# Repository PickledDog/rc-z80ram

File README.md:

# rc-z80ram
 CPU+RAM+Clock+Reset for RC2014

## Overview
This RC2014-compatible card provides a Z80 CPU, pageable RAM (fixed at the full 64K memory space, but disableable by the PAGE signal), and CLK and CLK2 signals. Reset supervision is provided.

## CPU
CPU is a regular Z80, with all signals brought out to the RC2014 Enhanced bus. Clock is always connected to the bus (and optionally generated locally - see below).

## Memory
RAM is provided by a single AS6C1008 128k x 8 SRAM chip. The chip may be optionally disabled (with JP1), and it may be configured to follow the bus PAGE signal (with JP2). This allows it to be paged out by compatible ROM cards or the BusRaider (currently untested). Only half of the chip is used; this part was picked because it is cheaper than 2x 62256 chips, and the extra chip select allows implementation of PAGEing without extra logic. Note that unlike the official RC2014 64K RAM card, PAGE disables *all* memory, not just the lower 32K (so this isn't compatible with the official RC2014 ROM card). The [PD104 ROM board](https://github.com/PickledDog/rc-rom) *is* supported, having been designed in tandem with this card.

### Why flat 64K?
This RAM on this card is primarily intended to be used with J.B. Langston's z80ctrl board and Rob Dobson's BusRaider board - it's really nice to use these with the freedom of having memory anywhere in the Z80 address space. To use this card with other memory systems (like the official RC2014 RAM/ROM cards or the 512K ROM 512K RAM card), disable the RAM, since it can't bring any benefit to them.

## Clock
A fixed 7.3728MHz clock can be provided by the board to CLK (and the Z80), selectable with JP3. This oscillator can further be divided and provided to CLK2, using JP4 and JP5:

| Divisor | Clock     | Baud   |
| ------- | --------- | ------ |
|      /1 | 7.3728MHz | 115200 |
|      /2 | 3.6864MHz |  57600 |
|      /3 | 2.4576MHz |  38400 |
|      /4 | 1.8432MHz |  28800 |
|      /6 | 1.2288MHz |  19200 |
|      /8 | 0.9216MHz |  14400 |

The clocks only have a 50% duty cycle for /1 and /2 divisors - the others vary by divisor (so /3 is 33% duty, etc). This is tolerated by the Z80 SIO chip (which is the only device this board is intended to clock).

## Reset
No reset button is provided, but the included DS1233 reset supervisor will clean up reset pulses from other buttons and enforce a reset pulse during power-on. This is intended to be used with backplanes that provide a reset button and pullup resistor (which is most of them).

## Jumper settings
Refer to the back of the board for detailed jumper setting instructions.

## Standard vs Enhanced bus
While this card can be used on a Standard Bus backplane (like the RC2014 Backplane-5 or Backplane-8), the RAM is basically unusable (since there's no way to page it out or fill it through bus control). If you intend to use it this way, omit the RAM chip, 4017, and all jumpers except JP3. If you're looking for an Enhanced backplane, I recommend Stephen C Cousins' [SC112](https://smallcomputercentral.wordpress.com/sc112-modular-backplane-rc2014/) (optionally with [SC113](https://smallcomputercentral.wordpress.com/sc113-modular-backplane-rc2014/)).

## Part selection
Bill Of Materials and part references are below. In order to make the 50-pin RC2014 Enhanced bus connector, you'll need to take a 2x40-pin right-angle header and pull out most of the pins from the top row (needle-nose pliers work well). I recommend using gold-plated header for this - I use these ones from [Pololu](https://www.pololu.com/product/2668) or [Sparkfun](https://www.sparkfun.com/products/12792). The jumper headers can be snapped from regular (or double-row) breakaway header, for which eBay is substantially cheaper; the Mouser listings are provided for convenience.

The specified parts are just the ones I used, and can be substituted as needed - Mouser links provided for convenience and reference. If you wish to socket the oscillator, I strongly recommend using a turned-pin oscillator socket, like [this one](https://www.mouser.com/ProductDetail/535-1108800). Not only do these already have the unused pins removed, they grip the oscillator much better (the limited friction of only 4 pins makes them tend to fall out of standard sockets).

| Reference | Value | Qty | Mouser link |
| --------- | ----- | --- | ----------- |
| C1-C4 | 100nF ceramic | 4 | [KEMET C315C104M5U5TA](https://www.mouser.com/ProductDetail/C315C104M5U5TA7303) |
| C5 | 1nf ceramic | 1 | [KEMET C315C102K1R5TA](https://www.mouser.com/ProductDetail/C315C102K1R5TA) |
| J1/2 | 2x40 right-angle header | 1 | [3M 2380-5121TG](https://www.mouser.com/ProductDetail/2380-5121TG) |
| JP1/2 | 2x3 header | 1 | [Amphenol 10129381-906002BLF](https://www.mouser.com/ProductDetail/10129381-906002BLF) |
| JP3 | 1x2 header | 1 | [Amphenol 10129378-902002BLF](https://www.mouser.com/ProductDetail/10129378-902002BLF) |
| JP4 | 1x3 header | 1 | [Amphenol 10129378-903002BLF](https://www.mouser.com/ProductDetail/10129378-903002BLF) |
| JP5 | 2x5 header | 1 | [Amphenol 10129381-910002BLF](https://www.mouser.com/ProductDetail/10129381-910002BLF) |
| | jumpers | 5 | [Harwin M7583-46](https://www.mouser.com/ProductDetail/M7583-46)
| RN1 | Bussed 10kΩ×4 resistor | 1 | [Bourns 4605X-AP1-103LF](https://www.mouser.com/ProductDetail/4605X-AP1-103LF) |
| U1 | 8MHz Z80 | 1 | [Zilog Z84C0008PEG](https://www.mouser.com/ProductDetail/Z84C0008PEG) |
| | socket | 1 | [Amphenol DILB40P-223TLF](https://www.mouser.com/ProductDetail/DILB40P-223TLF) |
| U2 | AS6C1008 SRAM | 1 | [Alliance AS6C1008-55PCN](https://www.mouser.com/ProductDetail/AS6C1008-55PCN) |
| | socket | 1 | [Amphenol DILB32P-223TLF](https://www.mouser.com/ProductDetail/DILB32P-223TLF) |
| U3 | DS1233-5 | 1 | [Dallas/Maxim DS1233-5+](https://www.mouser.com/ProductDetail/700-DS1233-5) |
| U4 | CD74HC4017 | 1 | [TI CD74HC4017E](https://www.mouser.com/ProductDetail/595-CD74HC4017E) |
| X1 | 7.3728MHz oscillator | 1 | [CTS MXO45HS-3C-7M3728](https://www.mouser.com/ProductDetail/MXO45HS-3C-7M3728) |

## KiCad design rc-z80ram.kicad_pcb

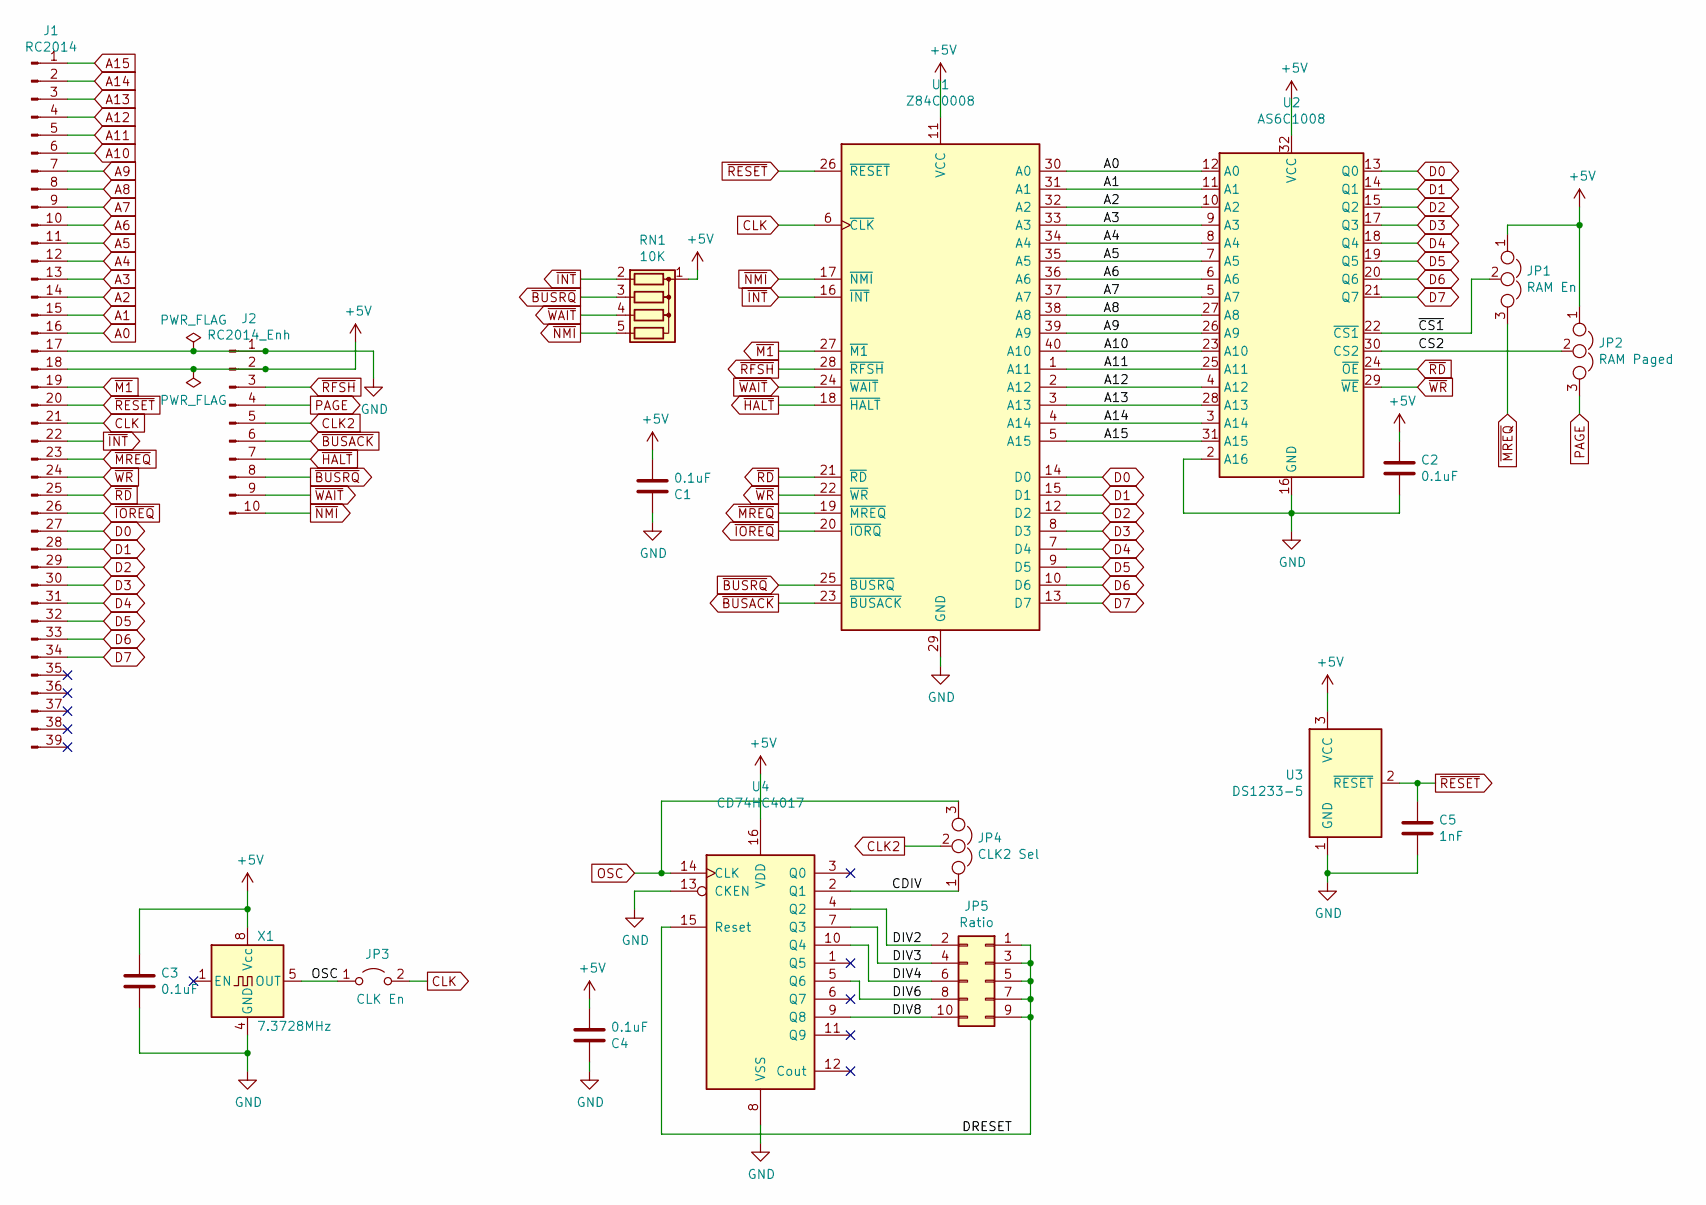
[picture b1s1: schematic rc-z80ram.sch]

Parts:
C1, C2, C3, C4: 0.1uF; C_Disc_D3.0mm_W1.6mm_P2.50mm
C5: 1nF; C_Disc_D3.0mm_W1.6mm_P2.50mm
J1: RC2014; PinHeader_1x39_P2.54mm_Vertical
J2: RC2014_Enh; PinHeader_1x10_P2.54mm_Vertical
JP1: RAM En; PinHeader_1x03_P2.54mm_Vertical
JP2: RAM Paged; PinHeader_1x03_P2.54mm_Vertical
JP3: CLK En; PinHeader_1x02_P2.54mm_Vertical
JP4: CLK2 Sel; PinHeader_1x03_P2.54mm_Vertical
JP5: Ratio; PinHeader_2x05_P2.54mm_Vertical
RN1: 10K; R_Array_SIP5
U1: Z84C0008; DIP-40_W15.24mm_LongPads
U2: AS6C1008; DIP-32_W15.24mm_LongPads
U3: DS1233-5; TO-92
U4: CD74HC4017; DIP-16_W7.62mm_LongPads
X1: 7.3728MHz; Oscillator_DIP-8

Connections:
+5V: C1.2, C2.2, C3.1, C4.2, J1.18, J2.2, JP1.1, JP2.1, RN1.1 (common), U1.11 (VCC), U2.32 (VCC), U3.3 (VCC), U4.16 (VDD), X1.8 (Vcc)
/CDIV: JP4.1, U4.2 (Q1)
/CS2: JP2.2, U2.30 (CS2)
/DIV2: JP5.2, U4.4 (Q2)
/DIV3: JP5.4, U4.7 (Q3)
/DIV4: JP5.6, U4.10 (Q4)
/DIV6: JP5.8, U4.5 (Q6)
/DIV8: JP5.10, U4.9 (Q8)
/DRESET: JP5.1, JP5.3, JP5.5, JP5.7, JP5.9, U4.15 (Reset)
/~CS1: JP1.2, U2.22 (~CS1)
A0: J1.16, U1.30 (A0), U2.12 (A0)
A1: J1.15, U1.31 (A1), U2.11 (A1)
A2: J1.14, U1.32 (A2), U2.10 (A2)
A3: J1.13, U1.33 (A3), U2.9 (A3)
A4: J1.12, U1.34 (A4), U2.8 (A4)
A5: J1.11, U1.35 (A5), U2.7 (A5)
A6: J1.10, U1.36 (A6), U2.6 (A6)
A7: J1.9, U1.37 (A7), U2.5 (A7)
A8: J1.8, U1.38 (A8), U2.27 (A8)
A9: J1.7, U1.39 (A9), U2.26 (A9)
A10: J1.6, U1.40 (A10), U2.23 (A10)
A11: J1.5, U1.1 (A11), U2.25 (A11)
A12: J1.4, U1.2 (A12), U2.4 (A12)
A13: J1.3, U1.3 (A13), U2.28 (A13)
A14: J1.2, U1.4 (A14), U2.3 (A14)
A15: J1.1, U1.5 (A15), U2.31 (A15)
CLK: J1.21, JP3.2 (B), U1.6 (~CLK~)
CLK2: J2.5, JP4.2
D0: J1.27, U1.14 (D0), U2.13 (Q0)
D1: J1.28, U1.15 (D1), U2.14 (Q1)
D2: J1.29, U1.12 (D2), U2.15 (Q2)
D3: J1.30, U1.8 (D3), U2.17 (Q3)
D4: J1.31, U1.7 (D4), U2.18 (Q4)
D5: J1.32, U1.9 (D5), U2.19 (Q5)
D6: J1.33, U1.10 (D6), U2.20 (Q6)
D7: J1.34, U1.13 (D7), U2.21 (Q7)
GND: C1.1, C2.1, C3.2, C4.1, C5.1, J1.17, J2.1, U1.29 (GND), U2.2 (A16), U2.16 (GND), U3.1 (GND), U4.8 (VSS), U4.13 (CKEN), X1.4 (GND)
OSC: JP3.1 (A), JP4.3, U4.14 (CLK), X1.5 (OUT)
PAGE: J2.4, JP2.3
~BUSACK: J2.6, U1.23 (~BUSACK~)
~BUSRQ: J2.8, RN1.3 (R2), U1.25 (~BUSRQ~)
~HALT: J2.7, U1.18 (~HALT~)
~INT: J1.22, RN1.2 (R1), U1.16 (~INT~)
~IOREQ: J1.26, U1.20 (~IORQ~)
~M1: J1.19, U1.27 (~M1~)
~MREQ: J1.23, JP1.3, U1.19 (~MREQ~)
~NMI: J2.10, RN1.5 (R4), U1.17 (~NMI~)
~RD: J1.25, U1.21 (~RD~), U2.24 (~OE)
~RESET: C5.2, J1.20, U1.26 (~RESET~), U3.2 (~RESET~)
~RFSH: J2.3, U1.28 (~RFSH~)
~WAIT: J2.9, RN1.4 (R3), U1.24 (~WAIT~)
~WR: J1.24, U1.22 (~WR~), U2.29 (~WE)

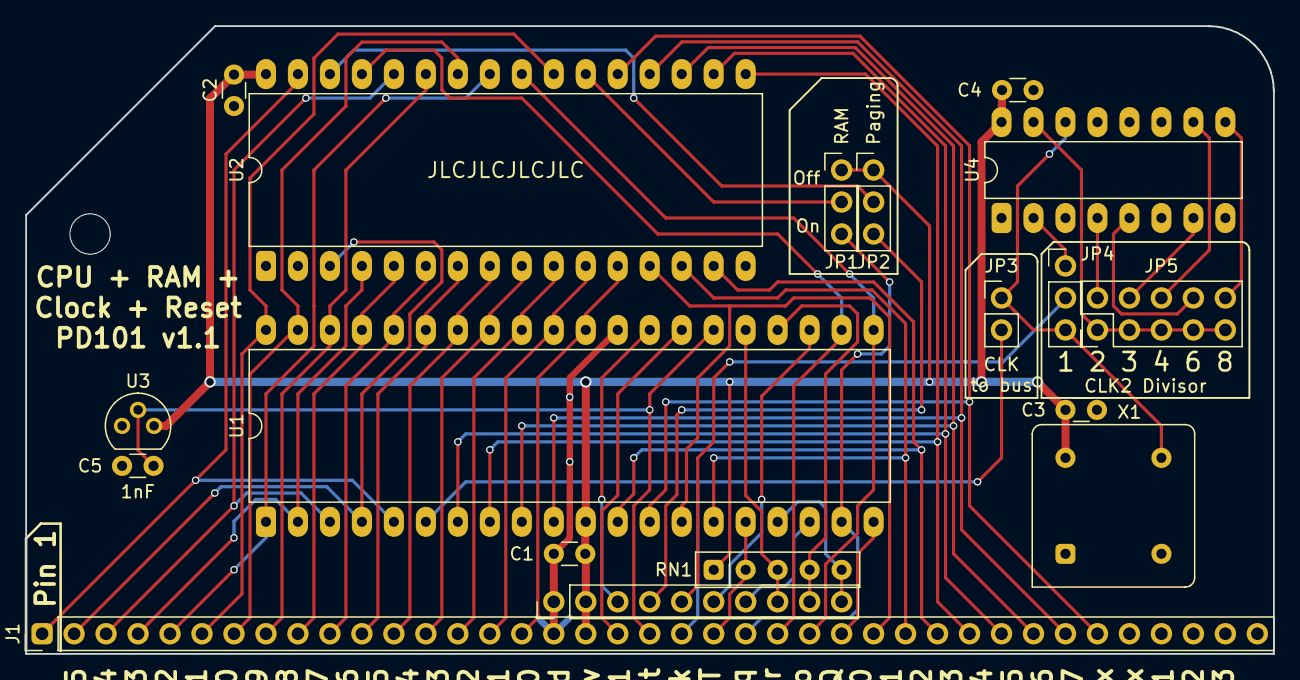
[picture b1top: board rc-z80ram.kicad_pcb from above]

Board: 2 copper layers, 99.1 x 49.9 mm, 18 parts (0 on the bottom side), 52 nets.

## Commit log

2020-11-23 Initial commit of rc-z80ram
    Initial commit of rc-z80ram/PD101.
2020-11-25 Move components, clean up routing
    Move components in order to shorten and neaten clock traces. Make jumpers easier to reach, move oscillator to bottom of card to reduce shorting risk.
2020-12-08 Added silkscreen decorations
    Added silkscreen decorations to resemble the general shape of RC2014 cards.
2020-12-11 Add BOM, tidy up schematic
2020-12-12 Forgot to update schematic
2020-12-27 Update README.md
    Added reference to PD104
2020-12-29 Add picture
2020-12-30 Add jumper reference shot
